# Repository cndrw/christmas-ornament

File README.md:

# christmas-ornament

Inspired by [heart-shape-key-charm](https://github.com/gschuk/heart-shape-key-charm).

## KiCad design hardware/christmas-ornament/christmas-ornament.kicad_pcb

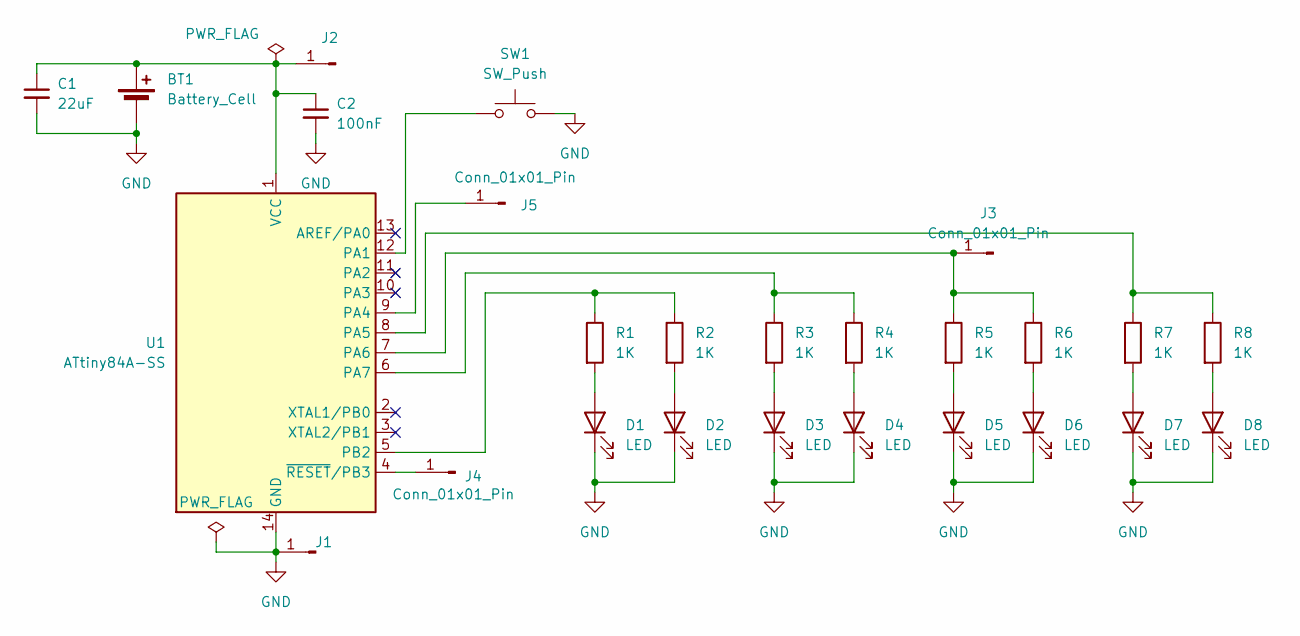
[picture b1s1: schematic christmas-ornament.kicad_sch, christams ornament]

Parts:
BT1: Battery_Cell; BatteryHolder_Keystone_1060_1x2032
C1: 22uF; C_0805_2012Metric
C2: 100nF; C_0805_2012Metric
D1, D2, D3, D4, D5, D6, D7, D8: LED; LED_D5.0mm
J1: TestPoint_Pad_D1.5mm
J2, J3, J4, J5: Conn_01x01_Pin; TestPoint_Pad_D1.5mm
R1, R2, R3, R4, R5, R6, R7, R8: 1K; R_0805_2012Metric
SW1: SW_Push; SW_Push_1P1T_NO_CK_KSC6xxJ
U1: ATtiny84A-SS; SOIC-14_3.9x8.7mm_P1.27mm

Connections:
GND: BT1.2 (-), C1.2, C2.2, D1.1 (K), D2.1 (K), D3.1 (K), D4.1 (K), D5.1 (K), D6.1 (K), D7.1 (K), D8.1 (K), J1.1 (Pin_1_1), SW1.2, U1.14 (GND)
unnamed: BT1.1 (+), C1.1, C2.1, J2.1 (Pin_1_1), U1.1 (VCC)
unnamed: D1.2 (A), R1.2
unnamed: D2.2 (A), R2.2
unnamed: D3.2 (A), R3.2
unnamed: D4.2 (A), R4.2
unnamed: D5.2 (A), R5.2
unnamed: D6.2 (A), R6.2
unnamed: D7.2 (A), R7.2
unnamed: D8.2 (A), R8.2
unnamed: J3.1 (Pin_1_1), R5.1, R6.1, U1.7 (PA6)
unnamed: J4.1 (Pin_1_1), U1.4 (~RESET/PB3)
unnamed: J5.1 (Pin_1_1), U1.9 (PA4)
unnamed: SW1.1, U1.12 (PA1)
unnamed: R7.1, R8.1, U1.8 (PA5)
unnamed: R3.1, R4.1, U1.6 (PA7)
unnamed: R1.1, R2.1, U1.5 (PB2)

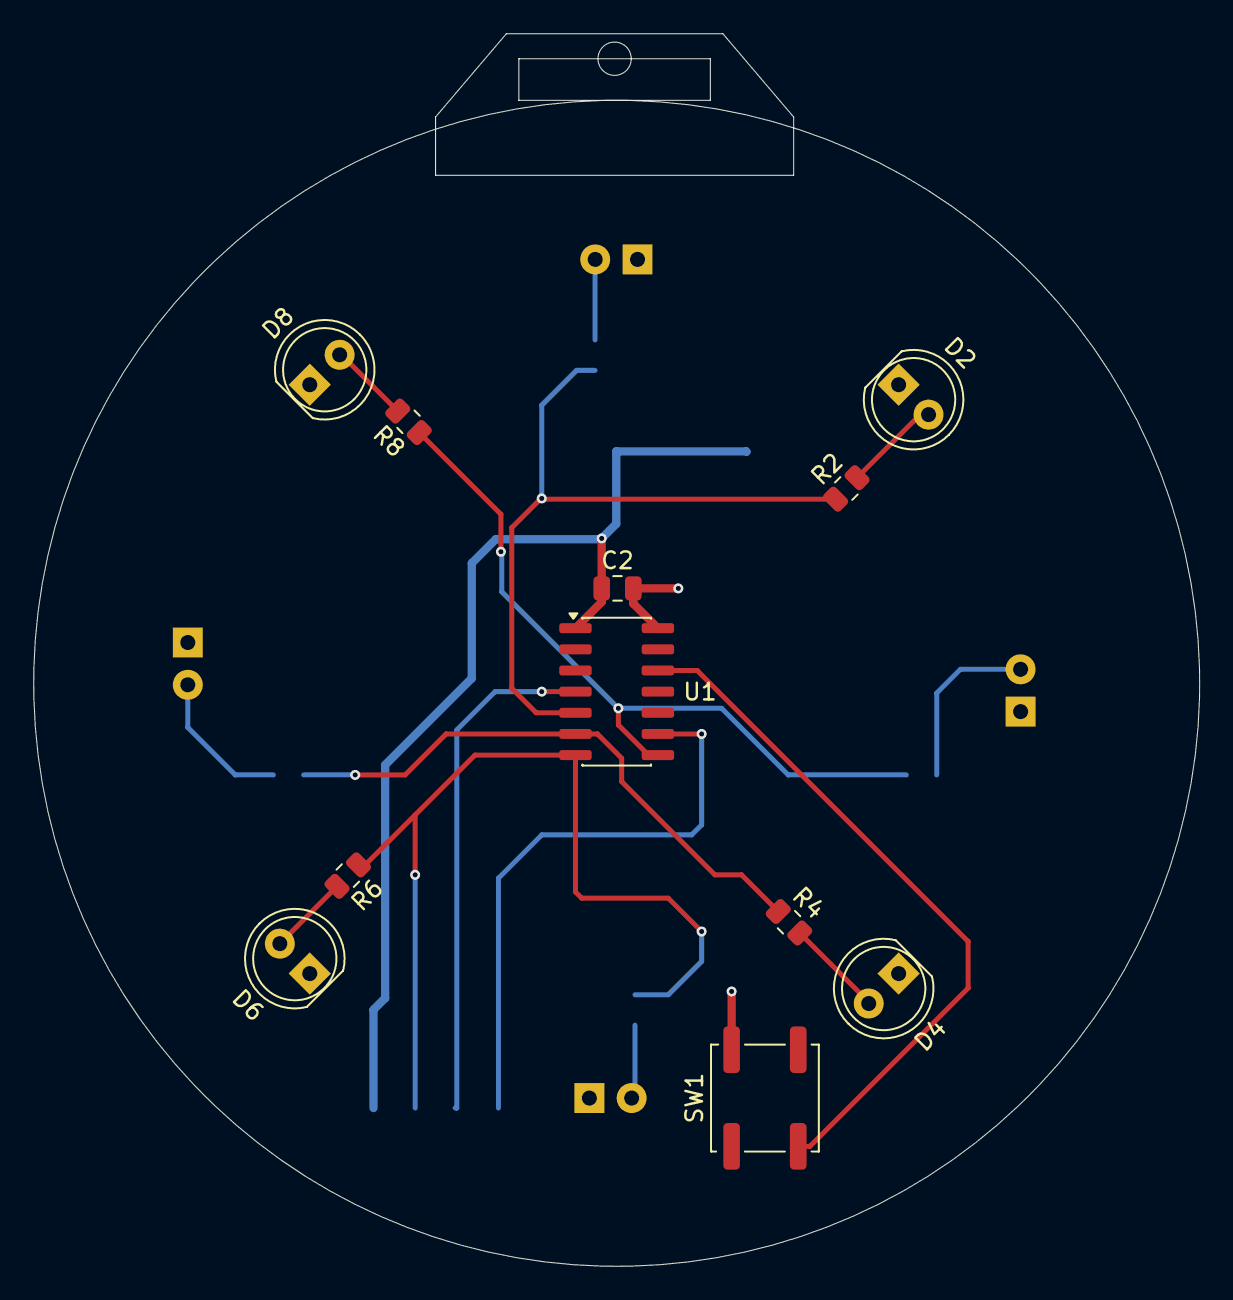
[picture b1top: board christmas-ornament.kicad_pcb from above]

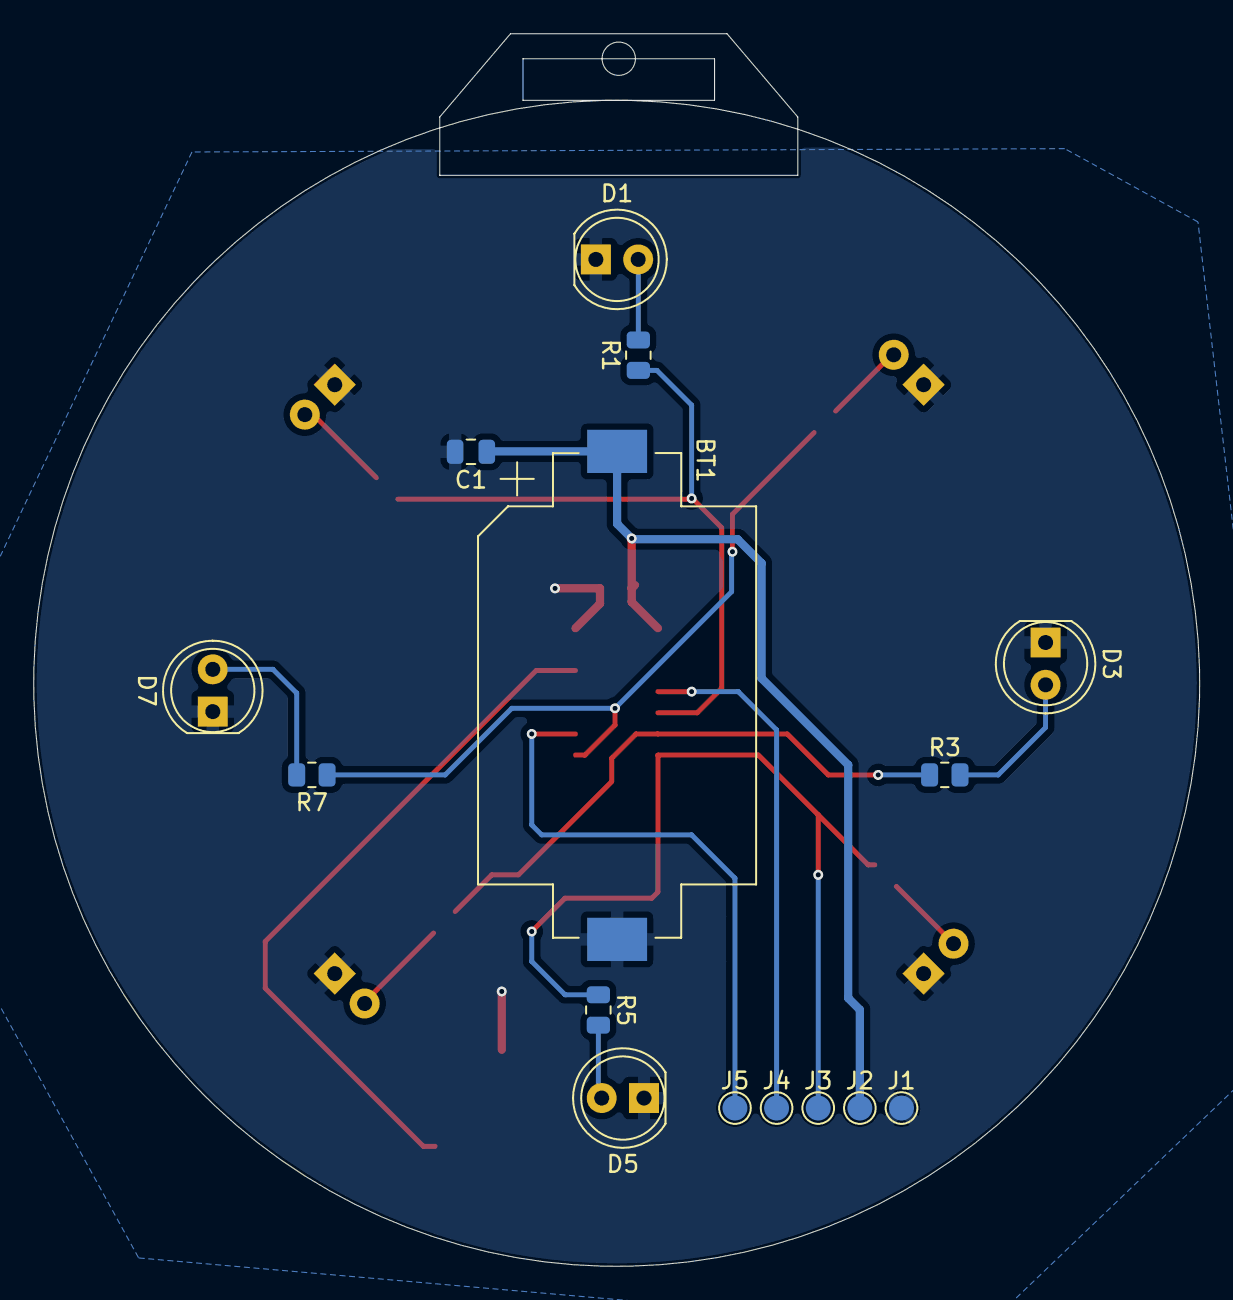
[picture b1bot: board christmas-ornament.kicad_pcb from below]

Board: 2 copper layers, 70.0 x 74.0 mm, 26 parts (15 on the bottom side), 17 nets.

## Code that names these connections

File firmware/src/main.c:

#define F_CPU 1000000UL

// avoid redefinition of Attiny84a flag
// but also make intellisens avaiable for the attiny84a macros
#ifndef __AVR_ATtiny84A__ 
#define __AVR_ATtiny84A__ 
#endif 

#include <avr/io.h>
#include <avr/interrupt.h>

#define __DELAY_BACKWARD_COMPATIBLE__ // make it possible to use _delay_ms with variables
#include <util/delay.h>

#define MS_TO_TICK_CONVERTION_FACTOR 0.06103515625
#define TICK_TO_MS_CONVERTION_FACTOR (1 / MS_TO_TICK_CONVERTION_FACTOR)
#define S_TO_TICK(x)  (x *  61.03515625)
#define MS_TO_TICK(x) (x *  MS_TO_TICK_CONVERTION_FACTOR)

#define N_LED 4

#define LED_EFFECT_SEMI_CYCLE_MIN_BRIGHTNESS 107

typedef uint8_t     u8;
typedef uint16_t    u16;
typedef uint32_t    u32;
typedef uint64_t    u64;

typedef int8_t      i8;
typedef int16_t     i16;

typedef struct {
    void(*init)(void);
    void(*update)(void);
}led_effect_t;

typedef struct {
    u8 pin;
    volatile u8 value;
}led_t;

typedef struct {
    led_t* led;
    u8 enabled;
    u8 t;
    i8 direction;
    u16 delay_ms;
}sparkle_blink_t;

volatile u64 ticks = 0; 

led_t leds[] = {
    { .pin = PB2, .value = 0 },
    { .pin = PA5, .value = 0 },
    { .pin = PA6, .value = 0 },
    { .pin = PA7, .value = 0 }
};

sparkle_blink_t sparke_blinks[] = {
    { .led = &leds[0], .enabled = 0, .t = 0, .direction = 1, .delay_ms = 800 },
    { .led = &leds[1], .enabled = 0, .t = 0, .direction = 1, .delay_ms = 800 },
    { .led = &leds[2], .enabled = 0, .t = 0, .direction = 1, .delay_ms = 800 },
    { .led = &leds[3], .enabled = 0, .t = 0, .direction = 1, .delay_ms = 800 }
};

sparkle_blink_t* possible_selection[3] = {0};
u8 schedule_lock = 0;
sparkle_blink_t* active_led = &sparke_blinks[0];
u64 last_update;

void noop(void) {}
void turn_off_leds(void);
void sparkle_effect_semi_cycle_init(void);
void sparkle_effect_full_cycle(void);
void sparkle_effect_semi_cycle(void);
void alternate_effect(void);
void build_up_effect(void);

const led_effect_t led_effects[] = {
    { .init = noop, .update = sparkle_effect_full_cycle },
    { .init = sparkle_effect_semi_cycle_init, .update = sparkle_effect_semi_cycle },
    { .init = noop, .update = alternate_effect },
    { .init = turn_off_leds, .update = build_up_effect }
};

u8 cur_effect = 3;

u32 seedx32 = 341259264;
u32 xorshift32()
{
    seedx32 ^= seedx32 << 13;
    seedx32 ^= seedx32 >> 17;
    seedx32 ^= seedx32 << 5;
    return seedx32 + TCCR1A * 2 - TCCR0B + TCCR0A;
}

u64 get_time_ms(void)
{
    return ticks * TICK_TO_MS_CONVERTION_FACTOR;
}

void setup_timer0(void)
{
    TCCR0A |= (1 << WGM00)  | (1 << WGM01) | // set fast-pwm mode
              (1 << COM0A1) | (1 << COM0B1); // non-inverting mode (clear oc0a on cmp match)

    TCCR0B |= (1 << CS00) | (1 << CS01);     // clk prescaler to N = 64 -> f_pwm = f_clk / N / 256 = 61,03515625

    TIMSK0 |= (1 << TOIE0); // overflow interrupt
}

void setup_timer1(void)
{
    TCCR1A |= (1 << WGM10) | (1 << COM1A1) | (1 << COM1B1); // non-inverting mode
    TCCR1B |= (1 << WGM12) | (1 << CS10) | (1 << CS11);     // clk prescaler to N = 64

    TIMSK1 |= (1 << OCIE1A) | (1 << OCIE1B);                // enable cmp match interrupt
}

u8 ease_in_cubic(const u8 x)
{
    return (u32)x * x * x / 65025;
}

u8 led_blink(sparkle_blink_t* const handle, const u8 min_value)
{
    handle->led->value = ease_in_cubic(handle->t);

    if (handle->t == UINT8_MAX) handle->direction = -1;
    if (handle->t == min_value) handle->direction = 1;

    handle->t += handle->direction;

    return handle->t == min_value;
}

u8 select_disabled_leds(sparkle_blink_t* const leds, const u8 size, sparkle_blink_t** out)
{
    u8 count = 0;
    for (u8 i = 0; i < size; i++)
    {
        if (!leds[i].enabled)
        {
            out[count] = &leds[i];
            count++;
        }
    }

    return count;
}

void sparkle_effect(const u8 min_brightness)
{
    if (!active_led->enabled && get_time_ms() - last_update > active_led->delay_ms)
    {
        active_led->enabled = 1;

        const u8 num_possible_selections = select_disabled_leds(sparke_blinks, N_LED, possible_selection);
        if (num_possible_selections > 0)
        {
            const u8 selected_led_idx = xorshift32() % num_possible_selections;
            active_led = possible_selection[selected_led_idx];
            // active_led->delay_ms = (xorshift32() % 2305) + 1050;
            active_led->delay_ms = (xorshift32() % 1800) + 1050;
        }
        else
        {
            schedule_lock = 1;
        }

        last_update = get_time_ms();
    }


    for (u8 i = 0; i < N_LED; i++)
    {
        if(sparke_blinks[i].enabled)
        {
            if (led_blink(&sparke_blinks[i], min_brightness))
            {
                sparke_blinks[i].enabled = 0;
                if (schedule_lock)
                {
                    active_led = &sparke_blinks[i];
                    schedule_lock = 0;
                }
            }
        }
    }
}

void turn_off_leds(void)
{
    for (u8 i = 0; i < N_LED; i++)
    {
        leds[i].value = 0;
    }
} 

void sparkle_effect_full_cycle()
{
    sparkle_effect(0);
}

void sparkle_effect_semi_cycle_init()
{
    for (u8 i = 0; i < N_LED; i++)
    {
        sparke_blinks[i].t = LED_EFFECT_SEMI_CYCLE_MIN_BRIGHTNESS;
        leds[i].value = ease_in_cubic(LED_EFFECT_SEMI_CYCLE_MIN_BRIGHTNESS);
    }
}

void sparkle_effect_semi_cycle()
{
    sparkle_effect(LED_EFFECT_SEMI_CYCLE_MIN_BRIGHTNESS);
}

void alternate_effect(void)
{
    static u8 parity = 0;

    for (u8 i = 0; i < N_LED; i++)
    {
        leds[i].value = (i % 2 == parity) * UINT8_MAX;
    }

    parity = !parity;
    _delay_ms(600);
}

void handle_mode_switching(void)
{
    static u64 last_update = 0;
    static u8 cur_btn_state = 0;
    static u8 last_btn_state = 0;
    static u8 allow_btn_press = 1;

    // 'cause of input pullup the button is pressed on LOW
    cur_btn_state = (PINA & (1 << PA1)) == 0;

    // TODO: is das nicht einfach ein nested if anstatt diese ulgy variable?
    if (get_time_ms() - last_update > 400)
    {
        allow_btn_press = 1;
        last_update = get_time_ms();
    }

    if (allow_btn_press && cur_btn_state == 1 && last_btn_state == 0)
    {
        cur_effect = (cur_effect + 1) % 3;
        allow_btn_press = 0;
    }

    last_btn_state = cur_btn_state;
}

u8 get_lowest_value(const sparkle_blink_t* const leds, const u8 size)
{
    u8 lowest_value = UINT8_MAX;
    for (u8 i = 0; i < N_LED; i++)
    {
        if (leds[i].t < lowest_value)
        {
            lowest_value = leds[i].t;
        }
    }
    return lowest_value;
}

u8 get_highest_value(const sparkle_blink_t* const leds, const u8 size)
{
    u8 highest_value = 0;
    for (u8 i = 0; i < N_LED; i++)
    {
        if (leds[i].t > highest_value)
        {
            highest_value = leds[i].t;
        }
    }
    return highest_value;
}

void build_up_effect(void)
{
    static i8 direction = 1;

    u8 target_value = direction == 1 ? 
                      get_lowest_value(sparke_blinks, N_LED) : 
                      get_highest_value(sparke_blinks, N_LED);

    switch (target_value)
    {
        case 0: direction = 1; break;
        case UINT8_MAX: direction = -1; break;
    }

    // 2. get all leds which have this value
    u8 size = 0;
    for (u8 i = 0; i < N_LED; i++)
    {
        if (sparke_blinks[i].t == target_value)
        {
            possible_selection[size] = &sparke_blinks[i];
            size++;        
        }
    } 

    // 3. select random from possibles
    active_led = possible_selection[xorshift32() % size];
    active_led->t += 15 * direction;
    active_led->led->value = ease_in_cubic(active_led->t);

    _delay_ms(150);
}

int main(void)
{
    DDRB |= (1 << PB2);
    DDRA |= (1 << PA5) | (1 << PA6) | (1 << PA7);
    PORTA |= (1 << PA1); // input pullup

    setup_timer0();
    setup_timer1();

    sei();  // enable interrupt

    last_update = get_time_ms();
    led_effects[cur_effect].init();
    while (1)
    {
        handle_mode_switching();
        led_effects[cur_effect].update();
        _delay_ms(5);
    }

    return 0;
}

// time base for self made clock
// clk = 10^6 hz -> 10^(-6) s * 64 * 256 = 0,016384 s
// One tick is 0,016384 s | 61,03515625 hz
ISR(TIM0_OVF_vect)
{
    ticks++;
    OCR0A = leds[0].value;
    OCR0B = leds[1].value;
}

ISR(TIM1_COMPA_vect)
{
    OCR1A = leds[2].value;
}

ISR(TIM1_COMPB_vect)
{
    OCR1B = leds[3].value;
}

// TODO:
// - für semi_cycle effect können die timings angepasst werden, da der zyklus kürzer ist
